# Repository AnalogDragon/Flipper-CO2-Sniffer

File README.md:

[简体中文](README-zh.md)

# CO2 Sniffer

CO2 Sniffer is a BMP388 + SCD30 environmental monitor for the Flipper Zero. Plug
the board into the GPIO header and open the app to view CO2, temperature,
humidity, pressure and estimated altitude. Readings can also be saved to the
microSD card or sent to a computer over USB.
The software project in `SW/` was developed by OpenAI Codex.

## Main features

- Measures CO2, temperature, humidity and pressure, and estimates altitude from
  the pressure reading.
- Offers several live dashboard layouts and history graphs for all five values.
- Saves readings to CSV at a chosen interval and duration, or sends them to a
  computer over USB.
- Continues with the remaining sensor if one becomes unavailable and reconnects
  it automatically when possible.

To keep startup transients out of the trend, history graphs omit the first 10
seconds after the app starts or the SCD30 reconnects.

## Controls

Button functions change with the current screen. All actions below are short
presses unless marked as a hold.

| Current screen | Input | Function |
| -------------- | ----- | -------- |
| Dashboard | **LEFT** | Open **Data Recording** |
| Dashboard | **RIGHT** | Open the first history graph |
| History graph | **LEFT / RIGHT** | Show the previous / next graph; return to the dashboard at either end |
| Dashboard | **UP / DOWN** | Change the dashboard layout |
| History graph | **UP / DOWN** | Change the graph time scale |
| Dashboard / history graph | **BACK** | Open the clear-history prompt; press **OK** to clear or **BACK** to cancel |
| Data Recording | **UP / DOWN** | Select the interval, length or **Start** field |
| Data Recording | **OK** | Change the selected setting; start when **Start** is selected, or stop while recording |
| Changing a recording setting | **LEFT / RIGHT** | Choose the required value |
| Changing a recording setting / Data Recording | **BACK** | Finish the current change; when not changing a setting, return to the dashboard |
| SCD30 settings | **UP / DOWN**, **OK** | Choose a setting and change it, or open manual calibration |
| Manual-calibration input | **LEFT / RIGHT**, **UP / DOWN** | Select and adjust a digit; press **OK** to review the value |

The following functions require a button hold:

| Where | Input | Function |
| ----- | ----- | -------- |
| Data Recording, while not changing a setting | Hold **LEFT** for 2 seconds | Open SCD30 settings |
| While reviewing a manual-calibration value | Hold **OK** for 2 seconds | Start calibration after the progress bar completes |
| When no calibration or exit prompt is shown | Hold **OK** | Turn the always-on backlight on or off |
| Any page | Hold **BACK** | Open the exit prompt; press **OK** to exit or **BACK** to cancel |

## Data recording

Data recording is useful for tracking environmental changes over time. Press
**LEFT** from the dashboard to open **Data Recording**, choose the interval and
recording length, then select **Start**. Recording ends automatically at the
chosen time. For a continuous recording, or to stop early, press **OK**.

| Setting | Choices |
| ------- | ------- |
| Interval | 2 s, 5 s, 10 s, 30 s, 1 min |
| Length | 1 min, 5 min, 10 min, 30 min, 1 h, 2 h, 8 h, 24 h, continuous |

Files are saved in `/ext/co2_sniffer/` on the microSD card. Each filename
includes the start time, interval and recording length. Every row contains the
time, elapsed recording time and available sensor readings; values from a
temporarily unavailable sensor are left empty. A blinking `REC` badge means
recording is active. If `SD!` appears, check that the microSD card is available
and writable.

## SCD30 settings and calibration

From **Data Recording**, hold **LEFT** for 2 seconds to open **SCD30
Calibration**. It provides two everyday settings:

- **Pressure comp** uses the current pressure measured by the BMP388 to improve
  SCD30 measurement accuracy.
- **Auto calib (ASC)** lets the SCD30 adjust its baseline during long-term use.

Pressure compensation is on and ASC is off by default. The app remembers later
changes and uses them again at the next startup.

### Manual calibration

Manual calibration is recommended only when the reading has a clear offset and
a reliable CO2 reference concentration is available. Do not treat outdoor air
as an exact 400 ppm reference.

Before calibration, leave the sensor running in a stable reference environment
for at least two minutes and keep faces away from it. Select **Manual
calibration**, enter the actual reference concentration (`0400–2000 ppm`), and
press **OK** to review it. Hold **OK** for 2 seconds; calibration starts only
after the progress bar completes, using the value entered as its reference.

## Hardware

The board connects to the Flipper GPIO port through a 2.54 mm 1×10 pin header
and carries the following sensors:

| Device | Role | I2C address |
| ------ | ---- | ----------- |
| Sensirion SCD30 | CO2, temperature, humidity | 0x61 |
| Bosch BMP388 | temperature, pressure | 0x76 |

I2C runs on GPIO C0 (SCL) / C1 (SDA), and the board is powered from the
Flipper's 3V3/5V pins. KiCad schematic and PCB design sources are in `HW/`.

## Fault handling

If one sensor is temporarily disconnected, its readings are shown as
unavailable while the other sensor continues to work. The app attempts to
restore the connection automatically. If the screen reports that the I2C bus
cannot be recovered, exit the app and restart the Flipper as instructed.

## Layout

- `HW/` — KiCad schematic and PCB design sources.
- `SW/` — Flipper app sources.
- `3d/` — Printable enclosure files: a 3MF with Bambu Lab settings and the original STEP model.
- `PROTOCOL.md` — full USB CDC serial protocol documentation.
- `README-zh.md` — this document in Chinese.

## License

GPL-3.0, see [LICENSE](LICENSE).

## USB data output

To receive live readings on a computer, connect the Flipper over USB and select
the second virtual COM port detected by the system. The first port is reserved
for the Flipper CLI. Measurements use a binary frame format; see
**[PROTOCOL.md](PROTOCOL.md)** for the complete frame format and parsing details.

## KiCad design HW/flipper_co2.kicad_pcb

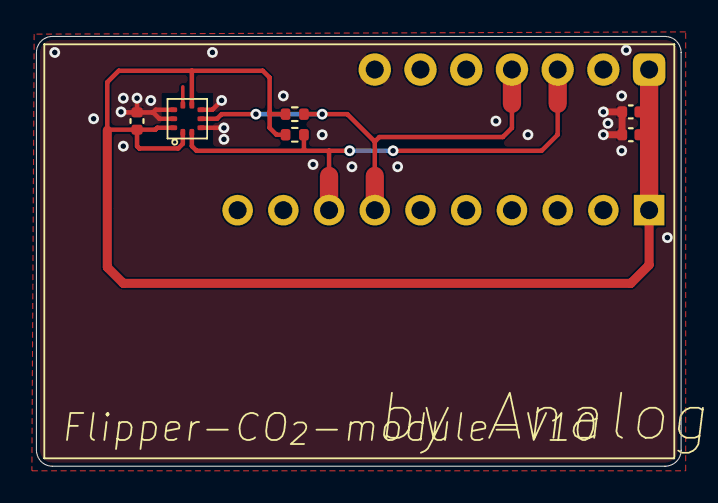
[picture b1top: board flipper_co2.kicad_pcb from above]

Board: 2 copper layers, 35.8 x 23.9 mm, 8 parts (1 on the bottom side), 4 nets.

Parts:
C1: 106/6.3V; C_0402_1005Metric
C2, C13: 104/50V; C_0402_1005Metric
J2: 2.54mm pinheader L=7.5mm; PinHeader_1x10_P2.54mm_Vertical
R1, R2: 4.7K; R_0402_1005Metric
U1: SCD30+2.54mm pinheader L=7.5mm; SCD30
U5: BMP388; LGA10-2x2-BMP388

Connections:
+3V3: C1.1, C2.1, C13.1, J2.1, R1.2, R2.2, U1.1 (VCC), U5.1 (VDDIO), U5.6 (CSB/I_{2}C_{EN}), U5.10 (VDD)
GND: C1.2, C2.2, C13.2, J2.3, U1.2 (GND), U1.7 (SEL), U5.3 (VSS), U5.5 (SDO/AD0), U5.8 (VSS), U5.9 (VSS)
IIC_SCL: J2.8, R1.1, U1.3 (SCL/TX), U5.2 (SCK)
IIC_SDA: J2.7, R2.1, U1.4 (SDA/RX), U5.4 (SDI/SDA)
